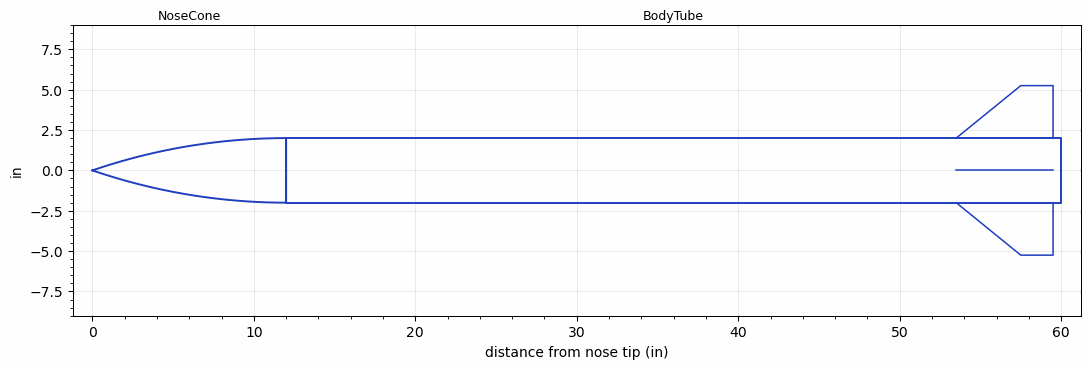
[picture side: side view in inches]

<RASAeroDocument>
 <FileVersion>2</FileVersion>
 <RocketDesign>
  <NoseCone>
   <Length>12</Length>
   <Diameter>4</Diameter>
   <Shape>Tangent Ogive</Shape>
   <Location>0</Location>
  </NoseCone>
  <BodyTube>
   <Length>47.9999</Length>
   <Diameter>4</Diameter>
   <Location>12</Location>
   <Fin>
    <Count>4</Count>
    <Chord>6</Chord>
    <Span>3.25</Span>
    <SweepDistance>4</SweepDistance>
    <TipChord>2</TipChord>
    <Thickness>0.125</Thickness>
    <Location>6.5</Location>
    <AirfoilSection>Square</AirfoilSection>
   </Fin>
  </BodyTube>
  <Surface>Smooth (Zero Roughness)</Surface>
  <ModifiedBarrowman>False</ModifiedBarrowman>
  <Turbulence>True</Turbulence>
  <SustainerNozzle>1</SustainerNozzle>
  <UseBooster1>False</UseBooster1>
  <UseBooster2>False</UseBooster2>
  <Comments>Extended controlled aerodynamic study: Hsq-nozzle1</Comments>
 </RocketDesign>
 <LaunchSite>
  <Altitude>0</Altitude>
  <Pressure>29.9214</Pressure>
  <RodAngle>0</RodAngle>
  <RodLength>6.5617</RodLength>
  <Temperature>59</Temperature>
  <WindSpeed>0</WindSpeed>
 </LaunchSite>
 <Recovery>
  <Altitude1>656.168</Altitude1>
  <Altitude2>0</Altitude2>
  <DeviceType1>Parachute</DeviceType1>
  <DeviceType2>None</DeviceType2>
  <Event1>True</Event1>
  <Event2>False</Event2>
  <Size1>24</Size1>
  <Size2>0</Size2>
  <EventType1>Apogee</EventType1>
  <EventType2>None</EventType2>
  <CD1>0.8</CD1>
  <CD2>0</CD2>
 </Recovery>
 <SimulationList>
  <Simulation>
   <SustainerEngine>I500T-14A  (AT)</SustainerEngine>
   <SustainerLaunchWt>14.5064</SustainerLaunchWt>
   <SustainerNozzleDiameter>1</SustainerNozzleDiameter>
   <SustainerCG>34.7639</SustainerCG>
   <SustainerIgnitionDelay>0</SustainerIgnitionDelay>
   <Booster1SeparationDelay>0</Booster1SeparationDelay>
   <Booster1IgnitionDelay>0</Booster1IgnitionDelay>
   <IncludeBooster1>False</IncludeBooster1>
   <Booster2Delay>0</Booster2Delay>
   <IncludeBooster2>False</IncludeBooster2>
   <TimetoApogee>8.790106</TimetoApogee>
   <MaxAltitude>1150.792</MaxAltitude>
   <MaxVelocity>267.925</MaxVelocity>
  </Simulation>
  <Simulation>
   <SustainerEngine>J570W  (AT)</SustainerEngine>
   <SustainerLaunchWt>15.1813</SustainerLaunchWt>
   <SustainerNozzleDiameter>1</SustainerNozzleDiameter>
   <SustainerCG>35.261</SustainerCG>
   <SustainerIgnitionDelay>0</SustainerIgnitionDelay>
   <Booster1SeparationDelay>0</Booster1SeparationDelay>
   <Booster1IgnitionDelay>0</Booster1IgnitionDelay>
   <IncludeBooster1>False</IncludeBooster1>
   <Booster2Delay>0</Booster2Delay>
   <IncludeBooster2>False</IncludeBooster2>
   <TimetoApogee>12.50019</TimetoApogee>
   <MaxAltitude>2556.784</MaxAltitude>
   <MaxVelocity>421.4901</MaxVelocity>
  </Simulation>
 </SimulationList>
</RASAeroDocument>
